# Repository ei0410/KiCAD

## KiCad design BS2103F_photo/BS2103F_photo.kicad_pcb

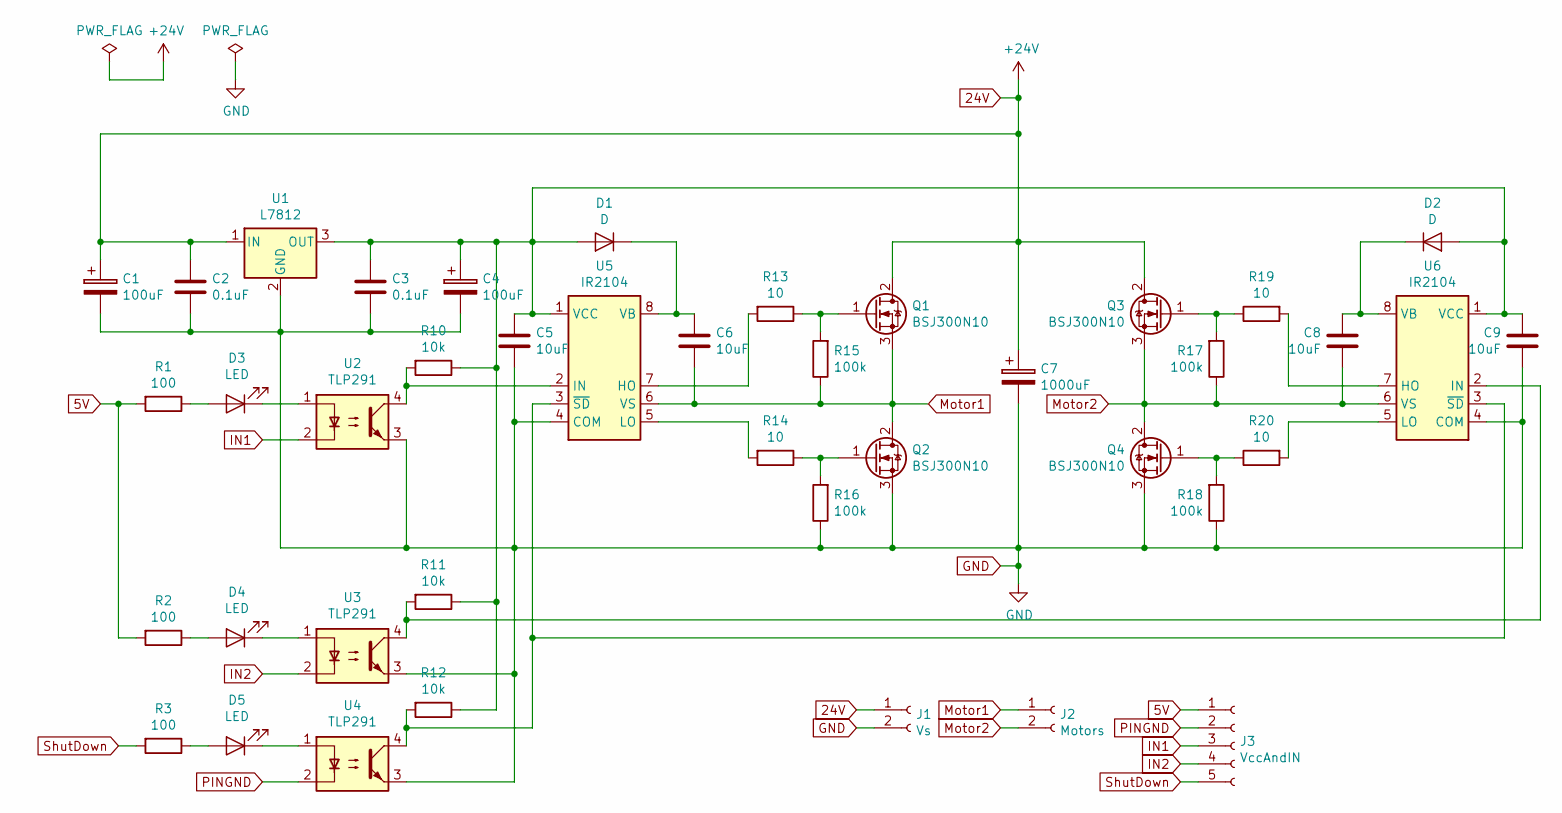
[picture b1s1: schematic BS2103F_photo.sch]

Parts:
C1, C4: 100uF; CP_Radial_D6.3mm_P2.50mm
C2, C3: 0.1uF; C_Disc_D4.3mm_W1.9mm_P5.00mm
C5, C6, C8, C9: 10uF; C_Disc_D4.3mm_W1.9mm_P5.00mm
C7: 1000uF; CP_Radial_D13.0mm_P5.00mm
D1, D2: D; D_1206_3216Metric
D3, D4, D5: LED; LED_0603_1608Metric_Pad1.05x0.95mm_HandSolder
J1: Vs; TerminalBlock_bornier-2_P5.08mm
J2: Motors; TerminalBlock_bornier-2_P5.08mm
J3: VccAndIN; JST_EH_B05B-EH-A_1x05_P2.50mm_Vertical
Q1, Q2, Q3, Q4: BSJ300N10; TO-263-2
R1, R2, R3: 100; R_0603_1608Metric_Pad1.05x0.95mm_HandSolder
R10, R11, R12: 10k; R_0603_1608Metric_Pad1.05x0.95mm_HandSolder
R13, R14, R19, R20: 10; R_0603_1608Metric_Pad1.05x0.95mm_HandSolder
R15, R16, R17, R18: 100k; R_0603_1608Metric_Pad1.05x0.95mm_HandSolder
U1: L7812; TO-252-2
U2, U3, U4: TLP291; SMDIP-4_W7.62mm
U5, U6: IR2104; SOIC-8_3.9x4.9mm_P1.27mm

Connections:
5V: J3.1, R1.2, R2.2
24V: C1.1, C2.1, C7.1, J1.1, Q1.2 (D), Q3.2 (D), U1.1 (IN)
GND: C1.2, C2.2, C3.2, C4.2, C5.2, C7.2, C9.2, J1.2, Q2.3 (S), Q4.3 (S), R16.1, R18.1, U1.2 (GND), U2.3, U3.3, U4.3, U5.4 (COM), U6.4 (COM)
IN1: J3.3, U2.2
IN2: J3.4, U3.2
Motor1: C6.2, J2.1, Q1.3 (S), Q2.2 (D), R15.1, U5.6 (VS)
Motor2: C8.2, J2.2, Q3.3 (S), Q4.2 (D), R17.1, U6.6 (VS)
unnamed: C3.1, C4.1, C5.1, C9.1, D1.2 (A), D2.2 (A), R10.1, R11.1, R12.1, U1.3 (OUT), U5.1 (VCC), U6.1 (VCC)
unnamed: C6.1, D1.1 (K), U5.8 (VB)
unnamed: C8.1, D2.1 (K), U6.8 (VB)
unnamed: D3.1 (K), U2.1
unnamed: D3.2 (A), R1.1
unnamed: D4.1 (K), U3.1
unnamed: D4.2 (A), R2.1
unnamed: D5.1 (K), U4.1
unnamed: D5.2 (A), R3.1
unnamed: Q1.1 (G), R13.1, R15.2
unnamed: Q2.1 (G), R14.1, R16.2
unnamed: Q3.1 (G), R17.2, R19.1
unnamed: Q4.1 (G), R18.2, R20.1
unnamed: R10.2, U2.4, U5.2 (IN)
unnamed: R11.2, U3.4, U6.2 (IN)
unnamed: R12.2, U4.4, U5.3 (~SD), U6.3 (~SD)
unnamed: R13.2, U5.7 (HO)
unnamed: R14.2, U5.5 (LO)
unnamed: R19.2, U6.7 (HO)
unnamed: R20.2, U6.5 (LO)
PINGND: J3.2, U4.2
ShutDown: J3.5, R3.2

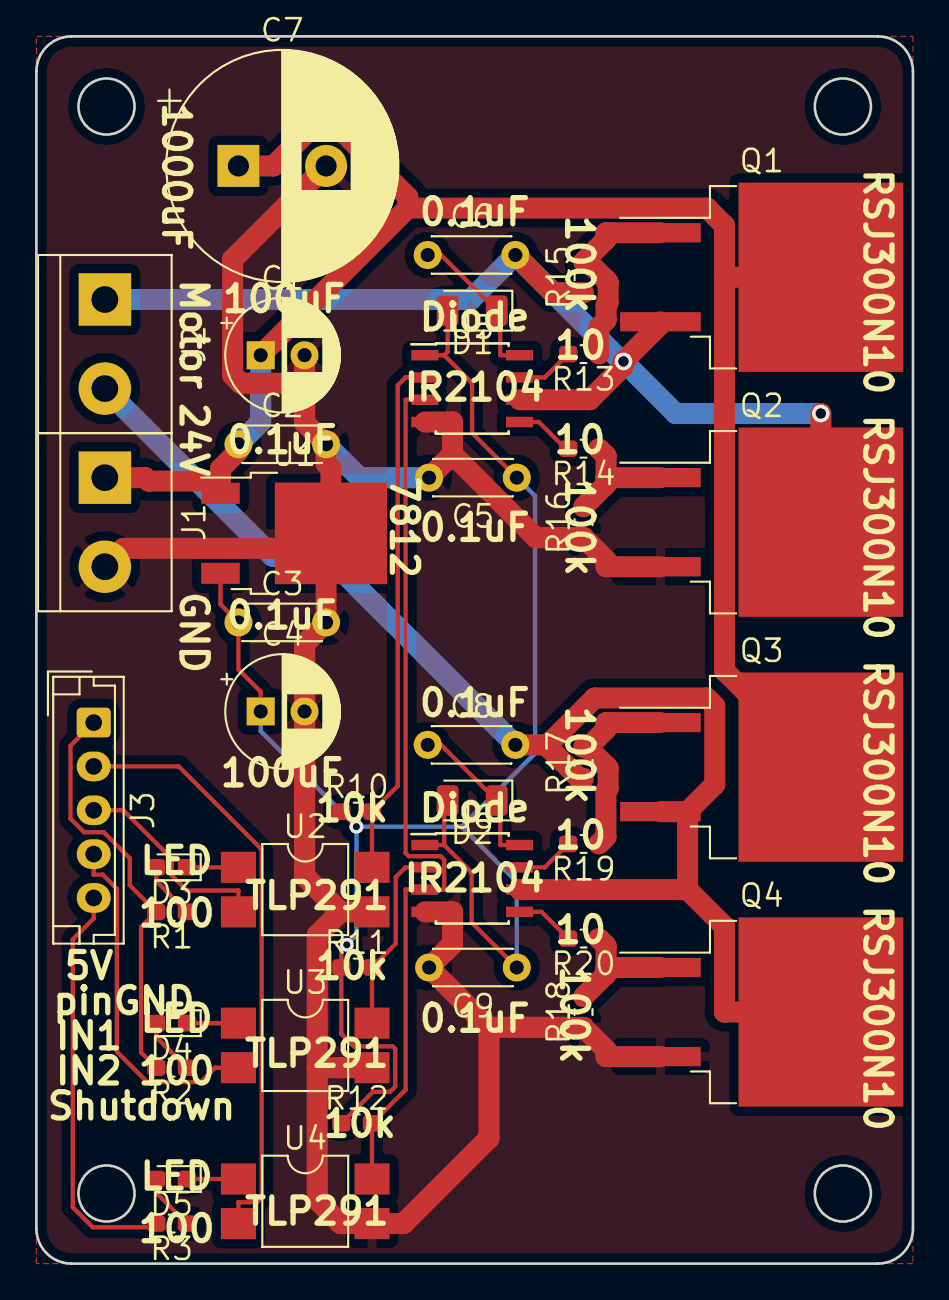
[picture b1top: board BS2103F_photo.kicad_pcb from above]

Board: 2 copper layers, 50.0 x 70.0 mm, 41 parts (0 on the bottom side), 29 nets.

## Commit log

2018-11-20 add MD
2018-11-22 add PCBdata
2018-11-22 add pcb.py
2018-11-23 add zipfile
2018-11-24 fusionPCB
2018-11-24 change pcb.py to fusionPCB.py
2018-11-24 remake zip file
